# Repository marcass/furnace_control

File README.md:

# furnace_control
Control a FUWI pellet boiler with arduino to improve smarts

After having 2 controal boards malfunction I have decided to roll my own with some improved modulation of fan speed and pellet feeding. Reporting or interface issues will be addressed also

Goals satisfied with this project are (not limited to):
* Reducing the need for cleaning of pellet boiler through better end of heat cycle managemtn of burner box (basically fanning the pellet wad until it burns out)
* Increasing efficiency of pellet usage by varying energy output of pellet boilder in accordance with demand (pid controlling fan, pellet feed time and pause feed time around setpoint). This has the added benefit of avoiding short-cycling and resultant ash buildup

#Components of system
1. Pellet boiler
2. Sensor network for house (managed by https://github.com/home-climate-control/dz ) - this will pull a pin low on arduino in boiler
3. Arduino controlled PCB in boiler
4. Communicatons server (communicates to arduino via usb-serial port and the rest of the world via MQTT)

This repository deals with the arduino sketch, the PCB and the communication interface on the server

# To perform headless-server update of arduino sketch
1. Stop python listener script on serial port "sudo systemctl stop arduino-attach.service"
2. Upload script to arduino: "make upload" (in root of git repo for furnace_control)
3. Start python listener script on serial port: "sudo systemctl start arduino-attach.service"

## Inputs from boiler
* Water temperature
* Auger shaft temperature
* Light sensor in flame box

## Outputs to boiler and assocaited hardware
* Auger motor to move pellets into flame box
* Fan to stoke fire
* 280W eleement to start fire
* Circ pump to pump heated water to radiators

## Safety
Hardware fail-safes are ideal as software may have problems that result in uncontrolled fire! Currently the boiler uses a device that breaks the neutral feed to the fan and element so it does not provide continuance when it is over a certain termperature (90 degrees C)
 * Error state pulls all relays to low
 * Idle state pulls fan and element to low

## States
1. Idle
2. Start_up
3. Heating
4. Cool_down
5. Error
6. Off

### Idle
 Wait for closed contact from 1-wire bus to transition into start_up. When contact closed: Blow fan to see if flame detected:
* if flame detected -> Heating
* if no flame -> Start_up

### Start up
1. Blow fan first to see if a flame will start
1. Pellet dump to get something for element to light
2. Element heating of pellet load
3. Gentle fan (phase angled to 30% or so) to start fire until light over threshold sensed
4. Pellet feed and full fan when light over threshold
5. Transition into heating when water temp over 50C

### Heating
1. PID control of trend of water temp and this affects fan speed through PWM and pellet feed rate
2. Start circ pump if over 50C
3. Pull fan relay low and circ pump high if temp over 85C
4. Transition to cool down if contact from 1-wire is opened

### Cool_down
1. Pull fan low and circ pump high until temp <60C
2. Transition to idle when below 60C

### Error
 Catch all that pulls fan adn element low

### Off
Don't start the boiler even if dz asks (button press and remote)

##Links
* Triac schematic for fan control (need up to 5A as heat diminishes capability
https://www.circuitar.com/media/product/25/files/Triac_v1.0.pdf

* Phase control for fan:
http://playground.arduino.cc/Main/ACPhaseControl
* ACPWM lib
http://playground.arduino.cc/Code/ACPWM
* Phase control explanation with varying of power output suggestions: http://electronics.stackexchange.com/questions/19273/when-should-i-fire-the-triacs-gate-when-controlling-an-inductive-load-ac-motor

##Connecton notes
* redundant fan_out connection at relay block in case on-board pahse angle not working
* P6 (240v outs) have the hardware thermostat (AB03 90.05) connected in pins 3 and 4 (polarity doesn't matter
  * when below 90C it is closed circuit
  * when above 90C it is open circuit
  * after opening it closes again at 75C
  * this (when closed circuit) supplies 240N to pins 1, 2 and 3 (pump, auger and element)
* 1-wire relay (hobby boards 8 channel) connects at pins 7 and 8 of P1 (low voltage input connector). When it is closed by control software the DZ_pin is pulled to ground
* 15k Ohm resistors need to be rated for 5w on 240VAC side (consumes 3.8W of power)
* 1.5k Resistor needs to be 50W on 240VAC side (consumes 38W of power) if constant power, but as MOC305 datasheet states:

"The power dissapation of this current limiting resistor and the triac driver is very small because the power triac carris the load current as soon as the current through the driver and current limiting resistor reaches the trigger current of teh power triac"

Switching times for the driver are 1 micro second and 4 micro seconds for the power triac

#Setup
Components of the sytsem are:
1. Boiler controller (arduino based on a PCB)
2. Communication interface on serial port
3. Display device(s)

##Boiler controller
PCB in kicad files in this repo
* Could do with 2 additional input pins for sensing hopper level
* Check that 5W resistors are up to the task of phase angle detection

## Communication interface on serial port
Uses:
* pyserial to capture data/print data to serial port (arduino) and insert into database
* paho-mqtt for subscribing/publishing to mosquitto broker
* mosquitto broker for managing infomration

###UDEV
See udev rules in repo:
* On insertion of aruduino usb assign symlink so pyserial can find device
* runs systemd service that starts the pythion script for managing stuff to and from arduino

###Data capture
Inserting data into influxdb and graphing via a vuejs frontend using plotly. See https://skibo.duckdns.org/sensors/#/graphs (repo here: https://github.com/marcass/esp32-sensornet/tree/master/sensornet)

##Device
Any mqtt client that runs on anything will display data from broker
* subscribe to topics:
  * boiler/switch (for turning on/off)
  * boiler/flame (for displaying flame value)
  * boiler/temp/auger
  * boiler/temp/water
  * boiler/temp/setpoint
  * boiler/messages (error messages)
  * boiler/state (state display)

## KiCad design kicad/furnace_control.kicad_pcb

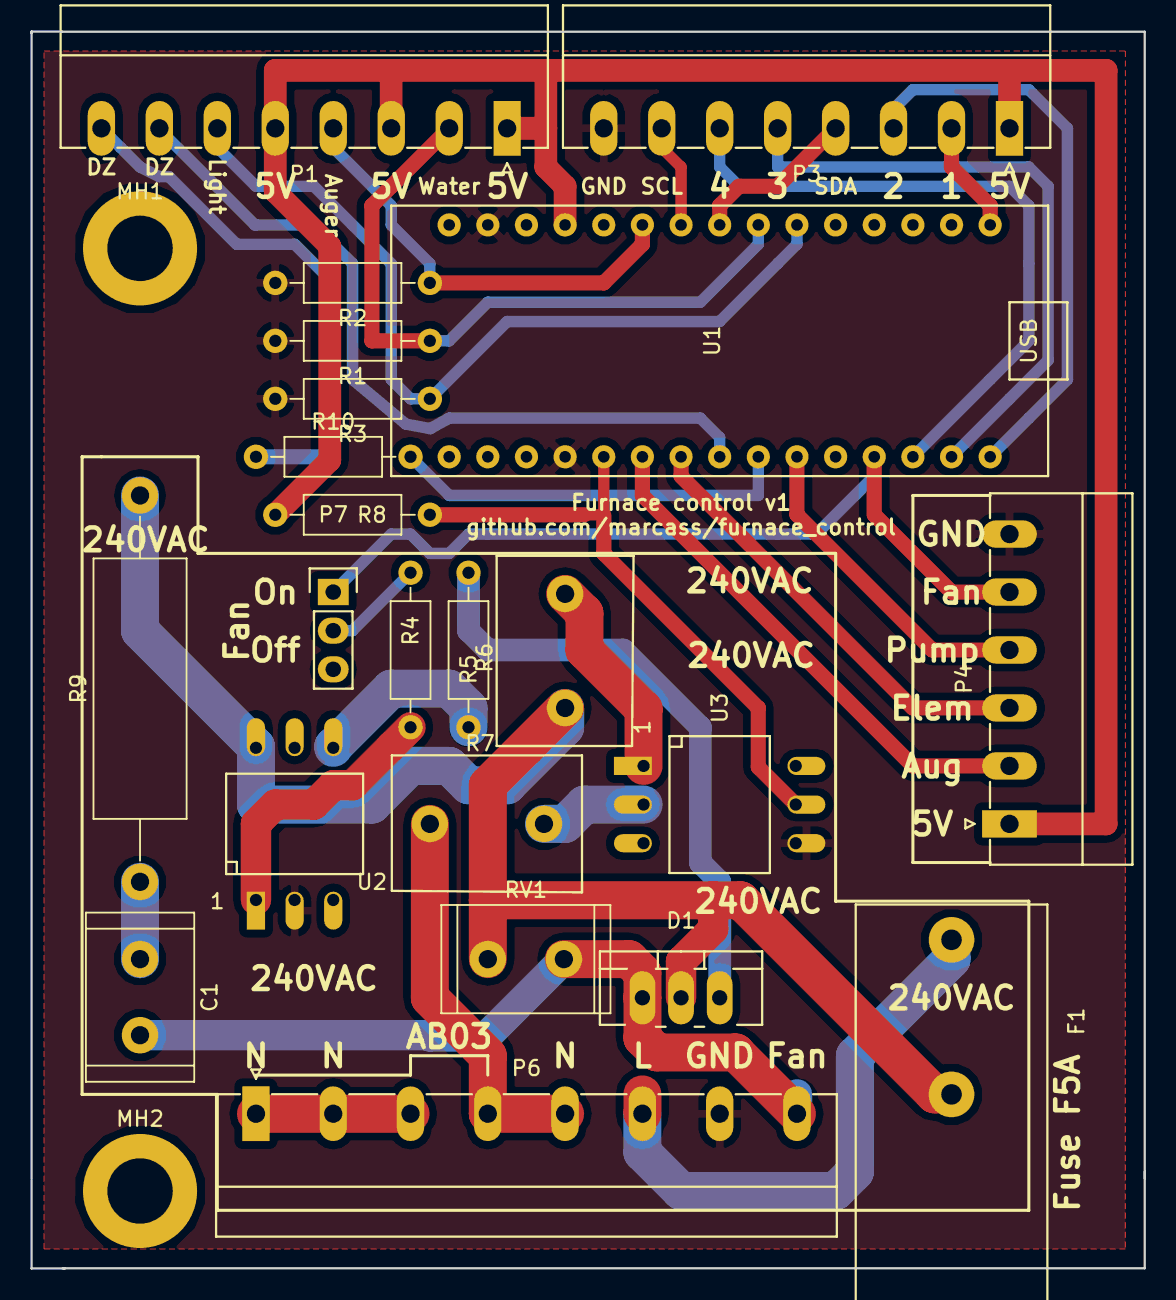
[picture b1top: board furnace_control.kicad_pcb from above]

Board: 2 copper layers, 73.2 x 81.3 mm, 24 parts (0 on the bottom side), 31 nets.

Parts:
C1: 0.01muF; R_Radial_Power_L11.0mm_W7.0mm_P5.00mm
D1: Q6015L5; TO-220_Neutral123_Vertical_LargePads
F1: Fuse; Fuseholder5x20_Horizontal_closed_Bulgin_FX0457
MH1, MH2: Mounting_hole; MountingHole_4.3mm_M4_DIN965_Pad
P1: CONN_01X08; PhoenixContact_MC-G_08x3.81mm_Angled
P3: LCD_Button; PhoenixContact_MC-G_08x3.81mm_Angled
P4: CONN_01X06; PhoenixContact_MC-G_06x3.81mm_Angled
P6: 240_CONN_Therm_on_3_4; PhoenixContact_MC-G_08x5.08mm_Angled
P7: Jumper; Pin_Header_Straight_1x03
R1, R2, R3, R8: 10k; R_Axial_DIN0207_L6.3mm_D2.5mm_P10.16mm_Horizontal
R4, R10: 220; R_Axial_DIN0207_L6.3mm_D2.5mm_P10.16mm_Horizontal
R5: 1.5k; R_Axial_DIN0207_L6.3mm_D2.5mm_P10.16mm_Horizontal
R6, R7: 15K; Resistor_5W_l12.5_w9_P7.5
R9: 33; R_Axial_DIN0617_L17.0mm_D6.0mm_P25.40mm_Horizontal
RV1: Varistor 600V; R_Radial_Power_L11.0mm_W7.0mm_P5.00mm
U1: arduino_nano; ArduinoNano
U2: MOC3052M; Optocoupler_6pin_wide_Stile-I
U3: H11AA1; Optocoupler_6pin_wide_Stile-I

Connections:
+5V: P1.1, P1.3, P1.5, P3.1, P4.1, R8.1, U1.12
/N: P6.1, P6.2, P6.3
/Neutral: P6.4, P6.5, R7.1
Button_1: P3.2, U1.1
Button_2: P3.3, U1.30
Button_3: P3.5, U1.29
Button_4: P3.6, U1.28
GND: P3.8, P4.6, P6.7, R1.2, R2.2, R3.2, U1.14, U1.19, U2.2, U3.4
unnamed: C1.1, R9.1
unnamed: C1.2, D1.1, P6.8, RV1.2
unnamed: D1.2, F1.2, R6.1, R9.2, RV1.1, U2.6
unnamed: D1.3, R5.1
unnamed: F1.1, P6.6
unnamed: P1.8, R10.1
unnamed: P7.2, R4.2
unnamed: R4.1, U2.1
unnamed: R5.2, U2.4
unnamed: R6.2, U3.1
unnamed: R7.2, U3.2
Out_auger: P4.2, U1.21
SCL: P3.7, U1.9
SDA: P3.4, U1.8
ac_in: R8.2, U1.20, U3.5
auger_temp: P1.4, R2.1, U1.10
dz_pin: P1.7, U1.23
dz_supply: R10.2, U1.24
element: P4.3, U1.22
fan_out: P4.5, P7.1, U1.27
light: P1.6, R3.1, U1.6
pump: P4.4, U1.25
water_temp: P1.2, R1.1, U1.7

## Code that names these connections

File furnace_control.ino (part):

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const int STATE_ERROR = 4;
const int STATE_OFF = 5;
//Buttons (numbers from left
const int BUTTON_1 = 13;
const int BUTTON_2 = 12;
const int BUTTON_3 = 11;
const int BUTTON_4 = 10;
//Outputs
const int PUMP = 7; //circ pump relay
const int FAN = 9; //fan relay. pin9 is a PWM pin and allows for analogWrite
const int AUGER = 3; //pellet auger relay
const int ELEMENT = 4; //fire starting element relay
//Inputs
const int WATER_TEMP = 3; //analogue pin 3
const int AUGER_TEMP = 6; //analogue pin 6
const int LIGHT = 2; //analogue pin 2 for flame detection
const int DZ_PIN = 5; // pin that is pulled up when 1-wire relay closes
const int DZ_SUPPLY = 6; //Need a pin to supply 5v that is passed to DZ_PIN when 1-wire relay closes
#define DETECT 2 //ac detection pin
#define GATE 9 //pwm pin
#define PULSE 4   //trigger pulse width (counts) that triac requires to fire one specified needs ~25mus
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unsigned long stop_start = 0; //for  fan short cycling
unsigned long start_feed_time = 0;//pellets
unsigned long start_feed_pause = 0;//pellets
unsigned long start_pump_time = 0;//pump short cycling
int on_wait; //variable for converting power to timer value
unsigned long feed_pause;//var for pellets puase time
unsigned long feed_time;//var for feed time
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  digitalWrite(DETECT, HIGH); //enable pull-up resistor
  pinMode(GATE, OUTPUT);      //TRIAC gate control
  digitalWrite(GATE, LOW);
  pinMode(PUMP, OUTPUT);
  digitalWrite(PUMP, LOW);
  pinMode(FAN, OUTPUT);
  digitalWrite(FAN, LOW);
  pinMode(AUGER, OUTPUT);
  digitalWrite(AUGER, LOW);
  pinMode(ELEMENT, OUTPUT);
  digitalWrite(ELEMENT, LOW);
  pinMode(DZ_SUPPLY, OUTPUT);
  digitalWrite(DZ_SUPPLY, LOW);
  //digitalWrite(A2, LOW);
  //Initialise inputs
  pinMode(DZ_PIN, INPUT_PULLUP);
  pinMode(BUTTON_1, INPUT_PULLUP);
  pinMode(BUTTON_2, INPUT_PULLUP);
  pinMode(BUTTON_3, INPUT_PULLUP);
  pinMode(BUTTON_4, INPUT_PULLUP);
  #ifdef pid
    //initialize the PID variables we're linked to
    fanPID.SetOutputLimits(30, 80); //percentage of fan power
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        fanend_start = 0;
      }
    }else{
      fanend_start = 0; //still have light so reset final blow
    }
  }else {
    fan(false, 0);
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void proc_idle() {
  housekeeping();
  //1-wire relay gets closed by DZ3
  if (digitalRead(DZ_PIN) == LOW) {
    state = STATE_START_UP;
//    reason = "";
//    #ifdef mqtt
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  //get flame_val average
  flame_value_median();
  //dz calls it: 1-wire relay gets closed by DZ3
  if (digitalRead(DZ_PIN) == HIGH) {
    if ((state == STATE_HEATING) || (state == STATE_START_UP)) {
      fanend_start = 0;//not going for end fan time so trying to reset variable here
      this_state = STATE_IDLE;
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
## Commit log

2017-02-14 Syntax correction in readme
2017-02-14 Started sketch and updated readme
2017-02-14 code additions
2017-02-15 MOre code updates
2017-02-15 Code update for arduino
2017-02-15 Added sketch for reading analogue sensors
2017-02-15 Updated links in readme
2017-02-15 adjusted control pins for internal pullup
2017-02-15 Added internal pullup to switching
2017-02-15 Added kicad files
2017-02-15 updated for phase angle control and schematic
2017-02-16 pcb started
2017-02-16 updated and checked PCB
2017-02-16 Updated README and notes on shcematic for power ratings of resistors
2017-02-16 updatred schematic
2017-02-17 updated schematic for parts ordered
2017-02-17 Added temperature readings to sketch and updated readme with power stuff
2017-02-17 udated pcb for fuse
2017-02-18 Added poser resitors to board
2017-02-21 updated sketch in prep for PID control
2017-02-23 further update to sketch
2017-02-27 phase angle stuff
2017-02-28 addeded tests, tidied code
2017-02-28 added test
2017-02-28 added tests
2017-02-28 sorted out light reading fuck up
2017-02-28 added test for zero crosses
2017-02-28 updated fan test stuff
2017-02-28 updated pcb
2017-02-28 tidying production code
2017-03-01 code tidying
2017-03-01 set up pid variables
2017-03-01 added pid test
2017-03-01 fixed code errors
2017-03-01 tested pid tests and modified code
2017-03-01 refined variables after testing
2017-03-01 started mqtt stuff
2017-03-02 refined publishing
2017-03-02 debug suff increased
2017-03-02 code refinements
2017-03-02 still need to sort fan
2017-03-02 hopefully sorted fan
2017-03-02 fan not sorted in start up
2017-03-02 fixed fan now?
2017-03-02 more code tidying
2017-03-03 rationalised fan management
2017-03-03 FANgit pull!
2017-03-03 fan fixed
2017-03-03 loop for sensors with delay inbetween
2017-03-03 started pyserial adn paho-mqtt stuff
2017-03-03 fan not fixed
2017-03-03 pump test
2017-03-03 smoothed state transitions
2017-03-03 pid problems sorted?
2017-03-03 Changed state change threshold
2017-03-04 sorted mqtt, rrd and pyserial
2017-03-04 added mqtt2rrd
2017-03-04 updated plot file
2017-03-04 code adjustments for boiler
2017-03-04 added lovely mqtt2rrd stuff (thanks)
2017-03-05 plotting nicely
2017-03-05 updated plot sketch for cp to remote
2017-03-05 fine tuning sketch for furnace comms
2017-03-05 updated systemd file
2017-03-05 more godam refinement
2017-03-05 reset start_count on turning from STATEOFF to STATE_ON
2017-03-05 systemd adn udev fiddling
2017-03-05 systemd files fiddled
2017-03-05 readme update
2017-03-05 more reporting via mqtt
2017-03-05 tweaked and twerked
2017-03-05 fiddled with pid tunings
2017-03-05 started rationalising mqtt publishing
2017-03-06 publishing lots of shit now via mqtt
2017-03-06 fine tuning
2017-03-06 more fiddling with hradware
2017-03-06 tidied up code
2017-03-07 python stuff
2017-03-07 tested median flame
2017-03-07 python stuff for serial pot aavailability
2017-03-07 fixed fan not stopping on cool down
2017-03-08 more python stuff
2017-03-08 fixed logic error
2017-03-08 fixed logic error. this time??
2017-03-08 stopped dumping too many pellets on second start
2017-03-08 strapped on fix for cool down
2017-03-08 python fiddling
2017-03-09 removed rrd stuff from tmp to see if deleted/overwritten elsewhere
2017-03-09 fixed plotting
2017-03-09 replaced serial_listen
2017-03-09 added Makefile
2017-03-09 some documentation within Makefile
2017-03-09 fiddled with timings
2017-03-09 more fiddling with sketch
2017-03-09 python connect/disconnect script
2017-03-10 updated config so not losing values in rrd
2017-03-11 added webserver for rrd graphs
2017-03-11 fiddled with start up sequence
2017-03-12 chnaged fan fucntion
2017-03-12 more fan sorting
2017-03-13 resetting stuff
2017-03-13 cooling hysteresis
2017-03-13 changing pid settings
2017-03-13 restart improvements
2017-03-14 changed cool_down logic
2017-03-14 updating python script for listening
2017-03-14 syncing repos
2017-03-14 publishig set point
2017-03-14 changed debug level on mqtt2rrd
2017-03-14 tidied up
2017-03-14 logic tweaking
2017-03-23 increased element time and dump, began dump_count reset logic
2017-05-08 updated switching of boiler to off and put limits on set point
2017-05-08 tidied up STATE_OFF
2017-05-08 updated README for uploading script
2017-05-08 updated setpoint publishing
2017-05-14 fiddled with cooling cycle
2017-05-29 Increase final fan blow time to get rid of more ash
2017-06-12 added retain flag for messages
2017-07-03 refined cool_to_stop
2017-07-04 cool to stop tweaking
2017-07-04 more timer fiddling
2017-07-06 more timeing issues at fan end
2017-07-11 furter timing changes
2017-07-13 changed flame thresh
2017-07-15 error reason tweaking
2017-07-16 auger tweak
2017-07-16 error error
2017-09-05 fixed trans to state_off when in idle
2017-09-05 semicolon
2017-09-07 fixed missing thing
2018-06-27 starting t ostup alerts
2018-06-28 updating alerts
2018-06-29 alerts need to be tested, but should be working now
2018-06-29 more fiddling
2018-06-29 updating dict problems
2018-06-29 what about now?
2018-06-29 can now manip outside of network and get alerts
2018-06-29 update gitignore
2018-07-04 Alerts should be working now
2018-07-19 started getting ready for front end
2018-07-21 setup a db
2018-07-22 writing data to db
2018-08-15 refactor of repo
2018-08-15 refactoring
2018-08-16 boiler as a sensor
2018-08-16 working via api
2018-08-17 getting more info from boiler
2018-08-19 not publishing temp, fixed?
2018-08-19 seems to be wokring
2018-08-20 resolved failiure of script
2018-08-31 updated influx line
2018-08-31 influx sorting
2018-09-10 kicking mqtt client back to life if excepts
2018-09-10 circular restarts of mqtt
2018-09-10 running and will self heal (hopefully)
2018-10-02 update fan test for new fan
2018-10-03 new fan in commision
2019-02-17 python3 ready
2019-07-31 dumped refresh tokens
2019-08-12 fixed stupid state
2019-08-14 moved telegram into docker
2019-08-19 updated so states are an integer
2019-08-20 trying to get states as numbers
2019-08-20 updating state publishing
2019-08-20 smoothign state transitions and removing text in states
2019-08-20 updated state type for influx
2020-04-12 added serial adaptor code
2020-04-12 having a status screen working and mqtt is tested
2020-04-12 no longer listening to serial
2020-04-13 working esp32 as a serial adaptor
2020-04-13 chnaged name to reflect function
2020-04-13 managing subscription a little better
2020-04-13 fixed code to turn boiler on/off
2020-04-13 updated some subscription stff i think
2020-04-14 set messages to be retained
2020-04-18 was still publishing stuff I shouldn't have been
2020-04-18 updated so it works
2020-04-29 we have a publishing problem
2020-08-18 prints for debugging
2020-08-21 getting info now
2020-08-21 udpated such that it is now publishing
2020-08-21 updated to give conistency between code bases
2020-08-26 updated serial listener
2020-08-27 got serial listener to not block
2020-08-27 added exception handling
2020-08-27 filterd pid types
2020-09-04 turning on and off works
